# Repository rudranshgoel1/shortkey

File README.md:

# shortkey

### Why did I make it?
bcz i need more hardware projects in my portfolio and also because it seemed like a fun hardware project which was kinda beginner friendly.

### What was the hardest part about this ?
honestly speaking, ROUTING THE LEDs OMFG.

Features:

- 47 keys with a 12x4 matrix
- nice!nano v2 as the main brain
- BLUETOOTH WIRELESS CONNECTIVITY
- 3.7v lithium battery for wireless
- M3 screws to hold the base and top part of the case together
- 0.91 inch oled display to see stats or anything like a virtual pet
- rgb backlit support with sk6812mini-e
- Custom case

### Schematic

### PCB 

### Case

### 3D view of all parts 

link to full 3d thing-
https://cad.onshape.com/documents/17a945b2f0455e7d6c526103/w/62132080eedaa9216da4dfe5/e/a80dcfc8a4a135788c505977?renderMode=0&uiState=6acfeb995e0cfdd1d2c4e421

## BOM

[BOM](BOM.csv)
|Name                    |Purpose                     |Quantity|Total Cost (USD)|Link                                                                                       |Distributor    |
|------------------------|----------------------------|--------|----------------|-------------------------------------------------------------------------------------------|---------------|
|nice!nano v2            |Main MCU                    |1       |10.17           |https://robu.in/product/pro-micro-nrf52840-development-board-compatible-with-nicenano-v2-0/|Robu           |
|Switches                |Switches for the keyboard   |47      |0               |SELF SOURCED                                                                               |SELF SOURCED   |
|Keycaps for the switches|Keycaps of the switches     |47      |0               |SELF SOURCED                                                                               |SELF SOURCED   |
|0.91 inch display       |Display                     |1       |2.2             |https://robu.in/product/0-91-inch-128x32-i2c-iic-serial-blue-oled-lcd-display-module/      |Robu           |
|SK6812 Mini-E           |LEDs for the switches       |47      |3.26            |https://www.lcsc.com/product-detail/C5149201.html?s_z=n_SK6812MINI-E                       |LCSC           |
|Case 3D Printed         |Case for the entire macropad|1       |0               |Printing Legion                                                                            |Printing Legion|
|PCB                     |Main PCBs                   |5       |9.78            |https://jlcpcb.com/                                                                        |JLPCB          |
|                        |                            |        |                |                                                                                           |               |
|                        |                            |        |25.41           |                                                                                           |               |

## Total Pricing

Final Price comes out to be 2,417.51 INR ($25.41) [ SHIPPING INCLUDED ]

The pricing might slightly vary due to flash sales, and dollar market trends.

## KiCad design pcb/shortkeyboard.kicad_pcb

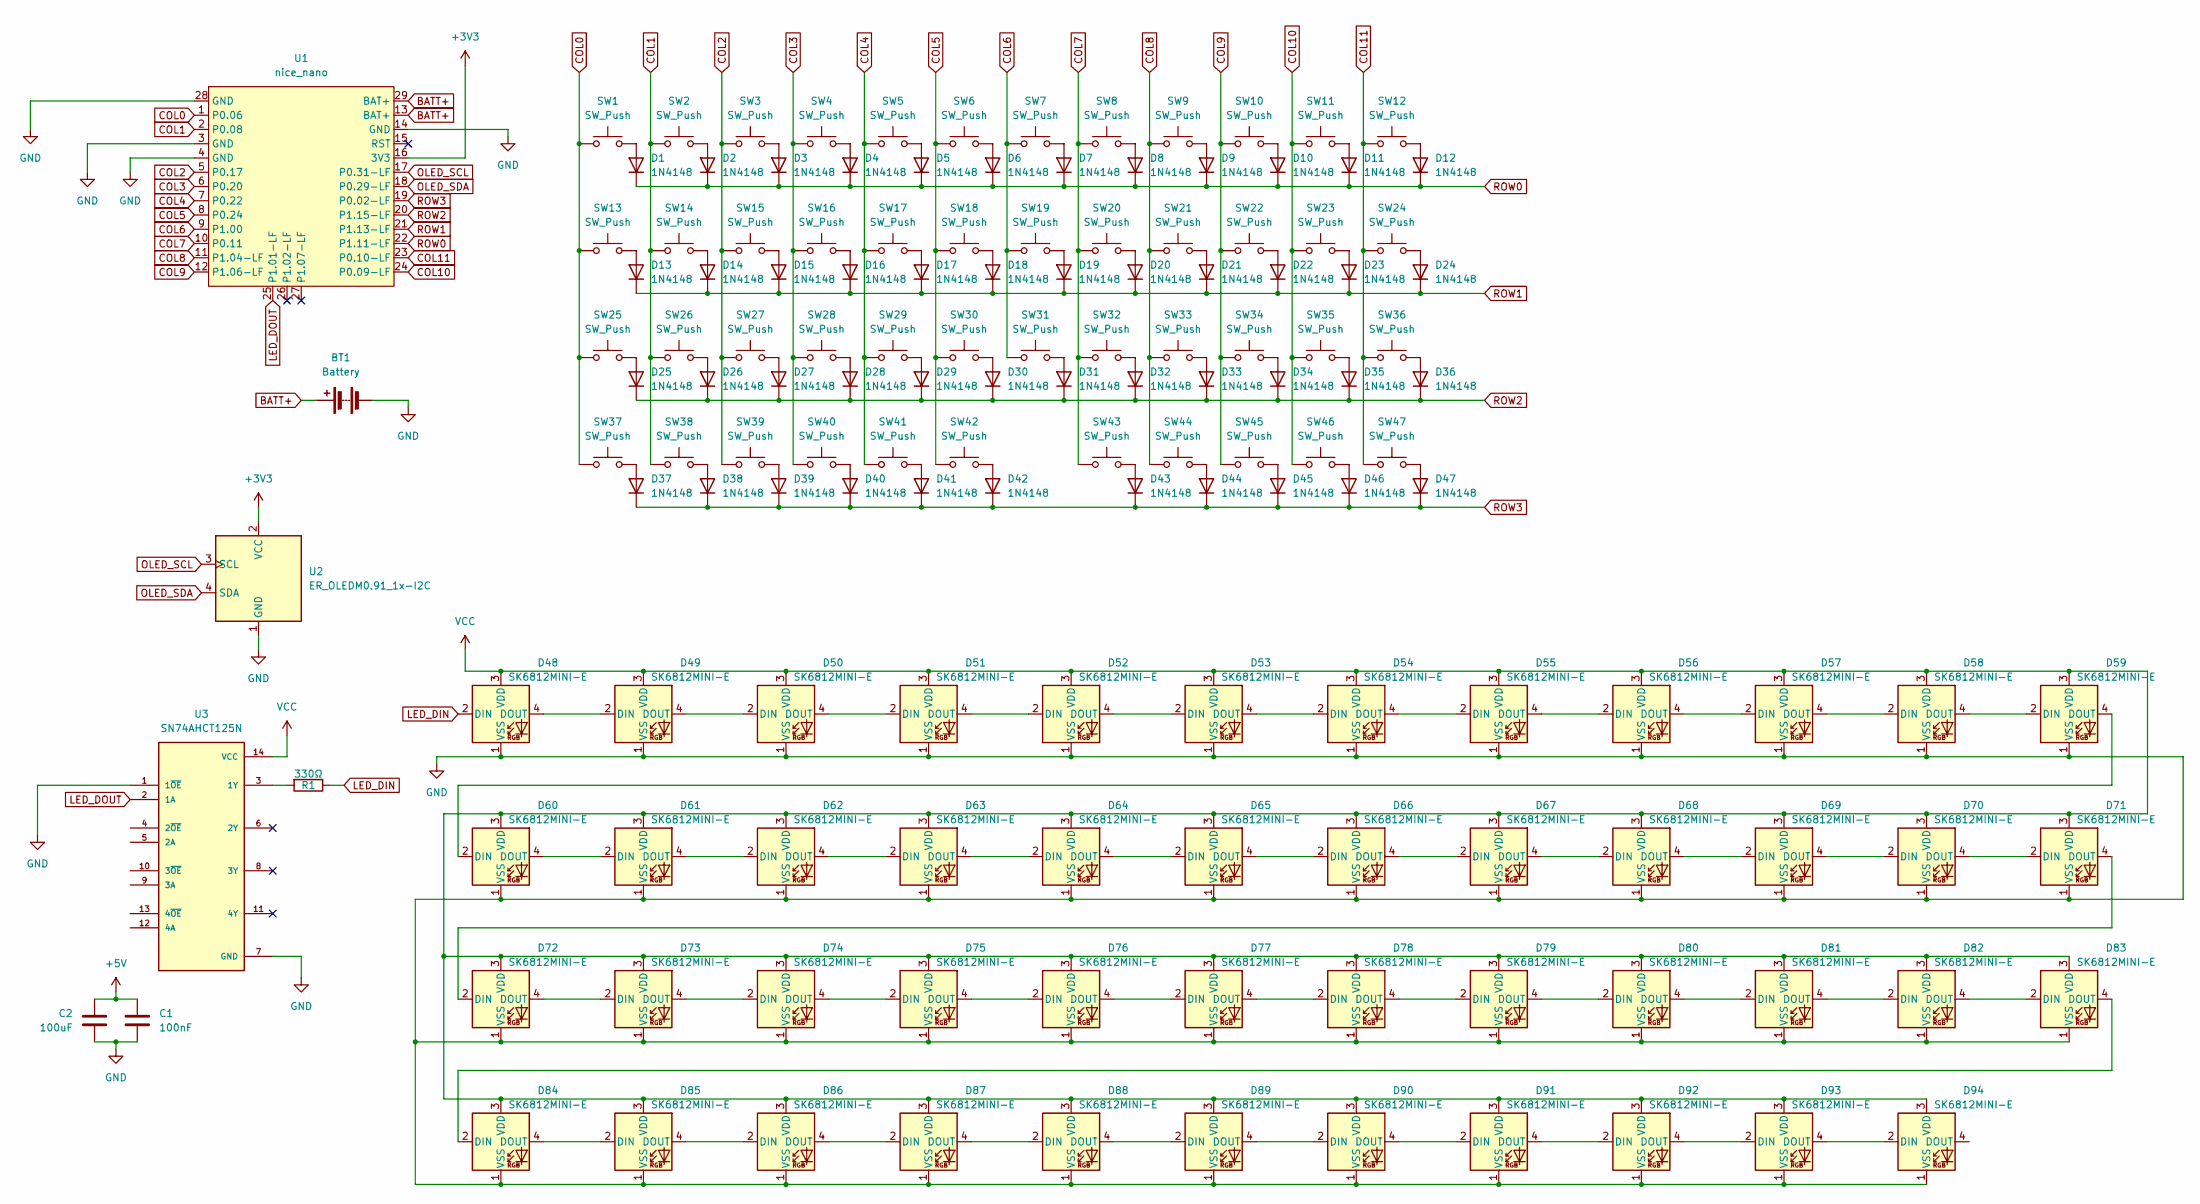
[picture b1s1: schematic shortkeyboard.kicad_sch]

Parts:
BT1: Battery; PinHeader_1x02_P2.54mm_Vertical
C1: 100nF; C_Disc_D5.0mm_W2.5mm_P5.00mm
C2: 100uF; CP_Radial_D5.0mm_P2.00mm
D1, D2, D3, D4, D5, D6, D7, D8, D9, D10, D11, D12, D13, D14, D15, D16, D17, D18, D19, D20, D21, D22, D23, D24, D25, D26, D27, D28, D29, D30, D31, D32, D33, D34, D35, D36, D37, D38, D39, D40, D41, D42, D43, D44, D45, D46, D47: 1N4148; D_DO-35_SOD27_P7.62mm_Horizontal
D48, D49, D50, D51, D52, D53, D54, D55, D56, D57, D58, D59, D60, D61, D62, D63, D64, D65, D66, D67, D68, D69, D70, D71, D72, D73, D74, D75, D76, D77, D78, D79, D80, D81, D82, D83, D84, D85, D86, D87, D88, D89, D90, D91, D92, D93, D94: SK6812MINI-E; LED_SK6812MINI-E_3.2x2.8mm_P1.5mm_ReverseMount
R1: 330Ω; R_0805_2012Metric_Pad1.20x1.40mm_HandSolder
SW1, SW2, SW3, SW4, SW5, SW6, SW7, SW8, SW9, SW10, SW11, SW12, SW13, SW14, SW15, SW16, SW17, SW18, SW19, SW20, SW21, SW22, SW23, SW24, SW25, SW26, SW27, SW28, SW29, SW30, SW31, SW32, SW33, SW34, SW35, SW36, SW37, SW38, SW39, SW40, SW41, SW43, SW44, SW45, SW46, SW47: SW_Push; SW_Cherry_MX_1.00u_PCB
SW42: SW_Push; SW_Cherry_MX_2.00u_PCB
U1: nice_nano; nice_nano_AH_USBup
U2: ER_OLEDM0.91_1x-I2C
U3: SN74AHCT125N; DIP794W45P254L1930H508Q14; PARTREV Q

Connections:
+3V3: U1.16 (3V3), U2.2 (VCC)
+5V: C1.1, C2.2
BATT+: BT1.1 (+), U1.13 (BAT+), U1.29 (BAT+)
COL0: SW1.1, SW13.1, SW25.1, SW37.1, U1.1 (P0.06)
COL1: SW2.1, SW14.1, SW26.1, SW38.1, U1.2 (P0.08)
COL2: SW3.1, SW15.1, SW27.1, SW39.1, U1.5 (P0.17)
COL3: SW4.1, SW16.1, SW28.1, SW40.1, U1.6 (P0.20)
COL4: SW5.1, SW17.1, SW29.1, SW41.1, U1.7 (P0.22)
COL5: SW6.1, SW18.1, SW30.1, SW42.1, U1.8 (P0.24)
COL6: SW7.1, SW19.1, SW31.1, U1.9 (P1.00)
COL7: SW8.1, SW20.1, SW32.1, SW43.1, U1.10 (P0.11)
COL8: SW9.1, SW21.1, SW33.1, SW44.1, U1.11 (P1.04-LF)
COL9: SW10.1, SW22.1, SW34.1, SW45.1, U1.12 (P1.06-LF)
COL10: SW11.1, SW23.1, SW35.1, SW46.1, U1.24 (P0.09-LF)
COL11: SW12.1, SW24.1, SW36.1, SW47.1, U1.23 (P0.10-LF)
GND: BT1.2 (-), C1.2, C2.1, D48.1 (VSS), D49.1 (VSS), D50.1 (VSS), D51.1 (VSS), D52.1 (VSS), D53.1 (VSS), D54.1 (VSS), D55.1 (VSS), D56.1 (VSS), D57.1 (VSS), D58.1 (VSS), D59.1 (VSS), D60.1 (VSS), D61.1 (VSS), D62.1 (VSS), D63.1 (VSS), D64.1 (VSS), D65.1 (VSS), D66.1 (VSS), D67.1 (VSS), D68.1 (VSS), D69.1 (VSS), D70.1 (VSS), D71.1 (VSS), D72.1 (VSS), D73.1 (VSS), D74.1 (VSS), D75.1 (VSS), D76.1 (VSS), D77.1 (VSS), D78.1 (VSS), D79.1 (VSS), D80.1 (VSS), D81.1 (VSS), D82.1 (VSS), D83.1 (VSS), D84.1 (VSS), D85.1 (VSS), D86.1 (VSS), D87.1 (VSS), D88.1 (VSS), D89.1 (VSS), D90.1 (VSS), D91.1 (VSS), D92.1 (VSS), D93.1 (VSS), D94.1 (VSS), U1.3 (GND), U1.4 (GND), U1.14 (GND), U1.28 (GND), U2.1 (GND), U3.1 (1~OE), U3.7 (GND)
LED_DIN: D48.2 (DIN), R1.1
LED_DOUT: U1.25 (P1.01-LF), U3.2 (1A)
unnamed: D1.2 (A), SW1.2
unnamed: D2.2 (A), SW2.2
unnamed: D3.2 (A), SW3.2
unnamed: D4.2 (A), SW4.2
unnamed: D5.2 (A), SW5.2
unnamed: D6.2 (A), SW6.2
unnamed: D7.2 (A), SW7.2
unnamed: D8.2 (A), SW8.2
unnamed: D9.2 (A), SW9.2
unnamed: D10.2 (A), SW10.2
unnamed: D11.2 (A), SW11.2
unnamed: D12.2 (A), SW12.2
unnamed: D13.2 (A), SW13.2
unnamed: D14.2 (A), SW14.2
unnamed: D15.2 (A), SW15.2
unnamed: D16.2 (A), SW16.2
unnamed: D17.2 (A), SW17.2
unnamed: D18.2 (A), SW18.2
unnamed: D19.2 (A), SW19.2
unnamed: D20.2 (A), SW20.2
unnamed: D21.2 (A), SW21.2
unnamed: D22.2 (A), SW22.2
unnamed: D23.2 (A), SW23.2
unnamed: D24.2 (A), SW24.2
unnamed: D25.2 (A), SW25.2
unnamed: D26.2 (A), SW26.2
unnamed: D27.2 (A), SW27.2
unnamed: D28.2 (A), SW28.2
unnamed: D29.2 (A), SW29.2
unnamed: D30.2 (A), SW30.2
unnamed: D31.2 (A), SW31.2
unnamed: D32.2 (A), SW32.2
unnamed: D33.2 (A), SW33.2
unnamed: D34.2 (A), SW34.2
unnamed: D35.2 (A), SW35.2
unnamed: D36.2 (A), SW36.2
unnamed: D37.2 (A), SW37.2
unnamed: D38.2 (A), SW38.2
unnamed: D39.2 (A), SW39.2
unnamed: D40.2 (A), SW40.2
unnamed: D41.2 (A), SW41.2
unnamed: D42.2 (A), SW42.2
unnamed: D43.2 (A), SW43.2
unnamed: D44.2 (A), SW44.2
unnamed: D45.2 (A), SW45.2
unnamed: D46.2 (A), SW46.2
unnamed: D47.2 (A), SW47.2
unnamed: D48.4 (DOUT), D49.2 (DIN)
unnamed: D49.4 (DOUT), D50.2 (DIN)
unnamed: D50.4 (DOUT), D51.2 (DIN)
unnamed: D51.4 (DOUT), D52.2 (DIN)
unnamed: D52.4 (DOUT), D53.2 (DIN)
unnamed: D53.4 (DOUT), D54.2 (DIN)
unnamed: D54.4 (DOUT), D55.2 (DIN)
unnamed: D55.4 (DOUT), D56.2 (DIN)
unnamed: D56.4 (DOUT), D57.2 (DIN)
unnamed: D57.4 (DOUT), D58.2 (DIN)
unnamed: D58.4 (DOUT), D59.2 (DIN)
unnamed: D59.4 (DOUT), D60.2 (DIN)
unnamed: D60.4 (DOUT), D61.2 (DIN)
unnamed: D61.4 (DOUT), D62.2 (DIN)
unnamed: D62.4 (DOUT), D63.2 (DIN)
unnamed: D63.4 (DOUT), D64.2 (DIN)
unnamed: D64.4 (DOUT), D65.2 (DIN)
unnamed: D65.4 (DOUT), D66.2 (DIN)
unnamed: D66.4 (DOUT), D67.2 (DIN)
unnamed: D67.4 (DOUT), D68.2 (DIN)
unnamed: D68.4 (DOUT), D69.2 (DIN)
unnamed: D69.4 (DOUT), D70.2 (DIN)
unnamed: D70.4 (DOUT), D71.2 (DIN)
unnamed: D71.4 (DOUT), D72.2 (DIN)
unnamed: D72.4 (DOUT), D73.2 (DIN)
unnamed: D73.4 (DOUT), D74.2 (DIN)
unnamed: D74.4 (DOUT), D75.2 (DIN)
unnamed: D75.4 (DOUT), D76.2 (DIN)
unnamed: D76.4 (DOUT), D77.2 (DIN)
unnamed: D77.4 (DOUT), D78.2 (DIN)
unnamed: D78.4 (DOUT), D79.2 (DIN)
unnamed: D79.4 (DOUT), D80.2 (DIN)
unnamed: D80.4 (DOUT), D81.2 (DIN)
unnamed: D81.4 (DOUT), D82.2 (DIN)
unnamed: D82.4 (DOUT), D83.2 (DIN)
unnamed: D83.4 (DOUT), D84.2 (DIN)
unnamed: D84.4 (DOUT), D85.2 (DIN)
unnamed: D85.4 (DOUT), D86.2 (DIN)
unnamed: D86.4 (DOUT), D87.2 (DIN)
unnamed: D87.4 (DOUT), D88.2 (DIN)
unnamed: D88.4 (DOUT), D89.2 (DIN)
unnamed: D89.4 (DOUT), D90.2 (DIN)
unnamed: D90.4 (DOUT), D91.2 (DIN)
unnamed: D91.4 (DOUT), D92.2 (DIN)
unnamed: D92.4 (DOUT), D93.2 (DIN)
unnamed: D93.4 (DOUT), D94.2 (DIN)
unnamed: R1.2, U3.3 (1Y)
OLED_SCL: U1.17 (P0.31-LF), U2.3 (SCL)
OLED_SDA: U1.18 (P0.29-LF), U2.4 (SDA)
ROW0: D1.1 (K), D2.1 (K), D3.1 (K), D4.1 (K), D5.1 (K), D6.1 (K), D7.1 (K), D8.1 (K), D9.1 (K), D10.1 (K), D11.1 (K), D12.1 (K), U1.22 (P1.11-LF)
ROW1: D13.1 (K), D14.1 (K), D15.1 (K), D16.1 (K), D17.1 (K), D18.1 (K), D19.1 (K), D20.1 (K), D21.1 (K), D22.1 (K), D23.1 (K), D24.1 (K), U1.21 (P1.13-LF)
ROW2: D25.1 (K), D26.1 (K), D27.1 (K), D28.1 (K), D29.1 (K), D30.1 (K), D31.1 (K), D32.1 (K), D33.1 (K), D34.1 (K), D35.1 (K), D36.1 (K), U1.20 (P1.15-LF)
ROW3: D37.1 (K), D38.1 (K), D39.1 (K), D40.1 (K), D41.1 (K), D42.1 (K), D43.1 (K), D44.1 (K), D45.1 (K), D46.1 (K), D47.1 (K), U1.19 (P0.02-LF)
VCC: D48.3 (VDD), D49.3 (VDD), D50.3 (VDD), D51.3 (VDD), D52.3 (VDD), D53.3 (VDD), D54.3 (VDD), D55.3 (VDD), D56.3 (VDD), D57.3 (VDD), D58.3 (VDD), D59.3 (VDD), D60.3 (VDD), D61.3 (VDD), D62.3 (VDD), D63.3 (VDD), D64.3 (VDD), D65.3 (VDD), D66.3 (VDD), D67.3 (VDD), D68.3 (VDD), D69.3 (VDD), D70.3 (VDD), D71.3 (VDD), D72.3 (VDD), D73.3 (VDD), D74.3 (VDD), D75.3 (VDD), D76.3 (VDD), D77.3 (VDD), D78.3 (VDD), D79.3 (VDD), D80.3 (VDD), D81.3 (VDD), D82.3 (VDD), D83.3 (VDD), D84.3 (VDD), D85.3 (VDD), D86.3 (VDD), D87.3 (VDD), D88.3 (VDD), D89.3 (VDD), D90.3 (VDD), D91.3 (VDD), D92.3 (VDD), D93.3 (VDD), D94.3 (VDD), U3.14 (VCC)

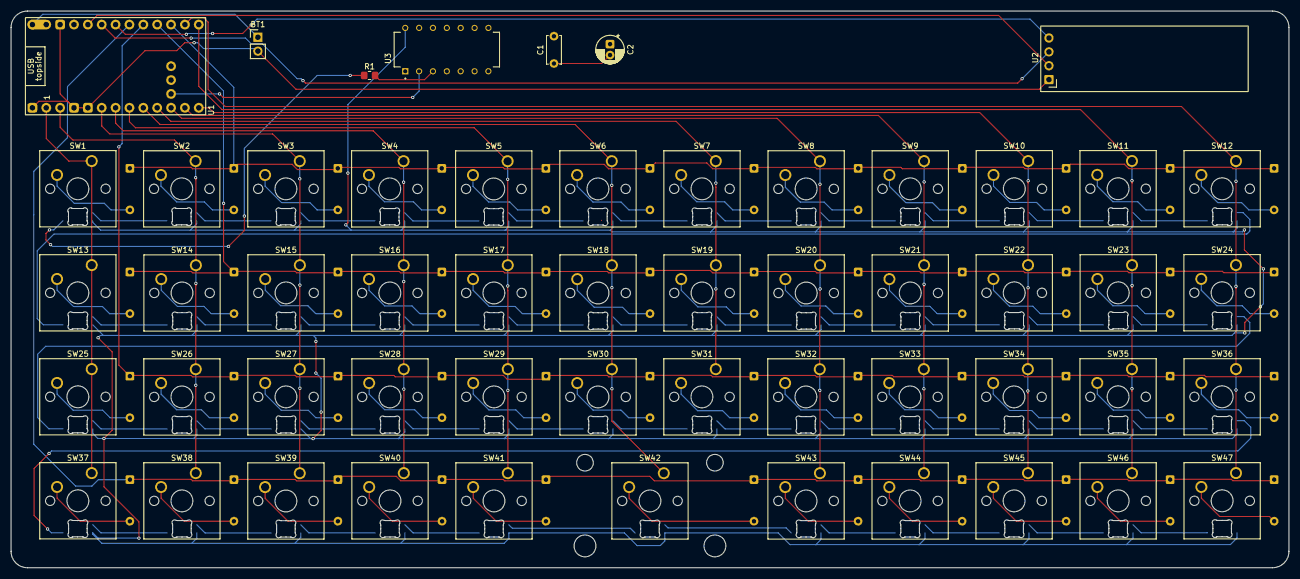
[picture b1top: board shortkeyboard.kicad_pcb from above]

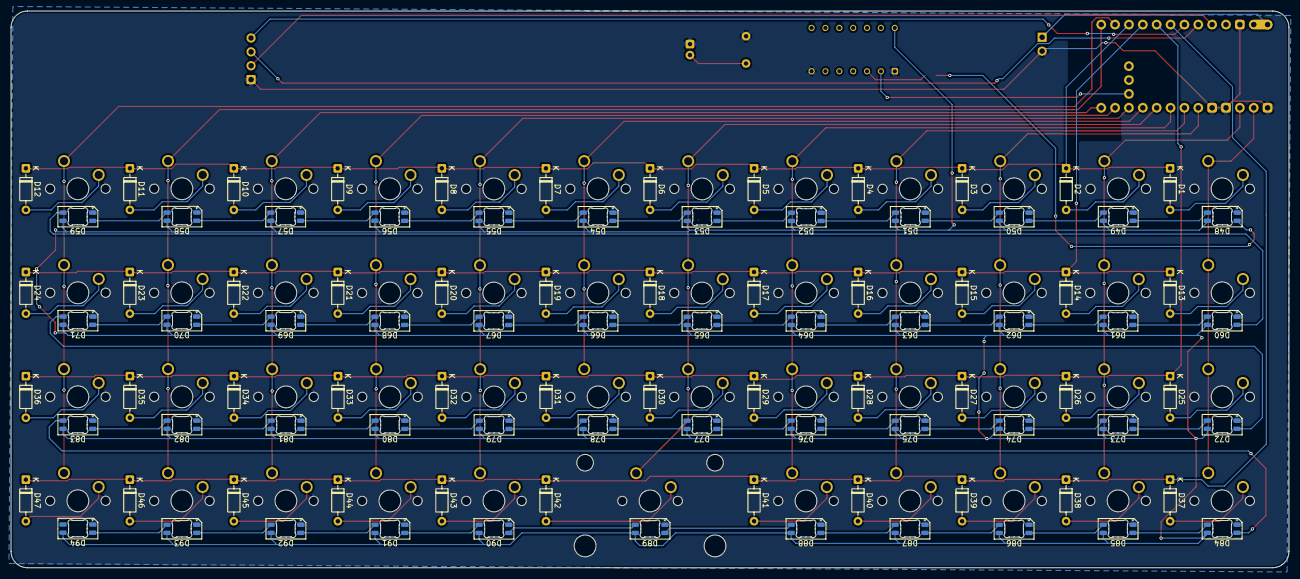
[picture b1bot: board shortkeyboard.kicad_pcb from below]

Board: 2 copper layers, 234.1 x 102.0 mm, 148 parts (94 on the bottom side), 119 nets.
